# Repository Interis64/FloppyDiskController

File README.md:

# FloppyDiskController
 Floppy disk controller card for Interis 64

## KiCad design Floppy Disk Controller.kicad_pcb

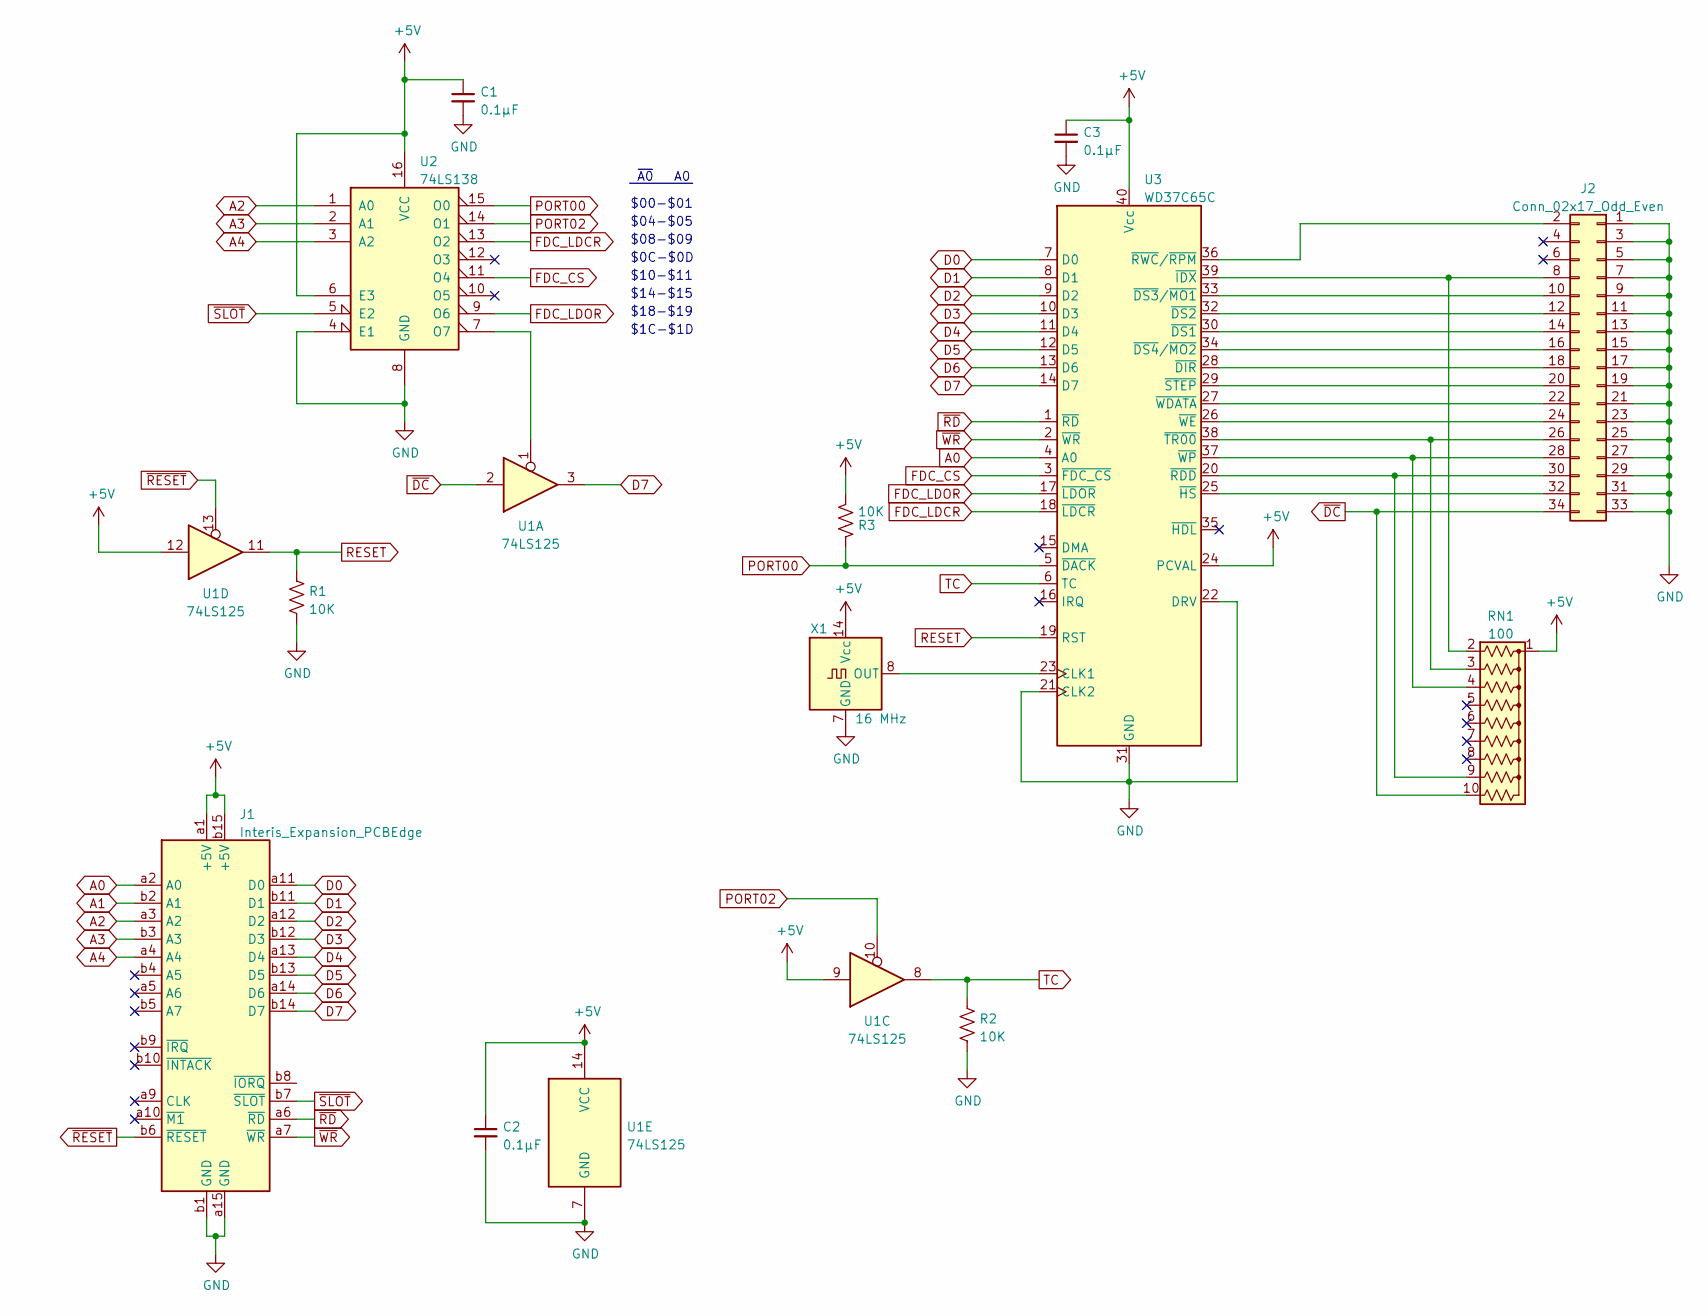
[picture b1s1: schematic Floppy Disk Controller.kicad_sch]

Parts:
C1, C2, C3: 0.1µF; C_Disc_D5.0mm_W2.5mm_P2.50mm
J1: Interis_Expansion_PCBEdge
J2: Conn_02x17_Odd_Even; IDC-Header_2x17_P2.54mm_Vertical
R1, R2, R3: 10K; R_Axial_DIN0207_L6.3mm_D2.5mm_P10.16mm_Horizontal
RN1: 100; R_Array_SIP10
U1: 74LS125; DIP-14_W7.62mm_Socket
U2: 74LS138; DIP-16_W7.62mm_Socket
U3: WD37C65C; DIP-40_W15.24mm_Socket
X1: 16 MHz; Oscillator_DIP-14

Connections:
+5V: C1.1, C2.1, C3.1, J1.a1 (+5V), J1.b15 (+5V), R3.1, RN1.1 (common), U1.9, U1.12, U1.14 (VCC), U2.6 (E3), U2.16 (VCC), U3.24 (PCVAL), U3.40 (Vcc), X1.14 (Vcc)
A0: J1.a2 (A0), U3.4 (A0)
A1: J1.b2 (A1)
A2: J1.a3 (A2), U2.1 (A0)
A3: J1.b3 (A3), U2.2 (A1)
A4: J1.a4 (A4), U2.3 (A2)
D0: J1.a11 (D0), U3.7 (D0)
D1: J1.b11 (D1), U3.8 (D1)
D2: J1.a12 (D2), U3.9 (D2)
D3: J1.b12 (D3), U3.10 (D3)
D4: J1.a13 (D4), U3.11 (D4)
D5: J1.b13 (D5), U3.12 (D5)
D6: J1.a14 (D6), U3.13 (D6)
D7: J1.b14 (D7), U1.3, U3.14 (D7)
FDC_CS: U2.11 (O4), U3.3 (~FDC_CS)
FDC_LDCR: U2.13 (O2), U3.18 (~LDCR)
FDC_LDOR: U2.9 (O6), U3.17 (~LDOR)
GND: C1.2, C2.2, C3.2, J1.a15 (GND), J1.b1 (GND), J2.1, J2.3, J2.5, J2.7, J2.9, J2.11, J2.13, J2.15, J2.17, J2.19, J2.21, J2.23, J2.25, J2.27, J2.29, J2.31, J2.33, R1.2, R2.1, U1.7 (GND), U2.4 (E1), U2.8 (GND), U3.21 (CLK2), U3.22 (DRV), U3.31 (GND), X1.7 (GND)
unnamed: J2.2, U3.36 (~RWC/~RPM)
unnamed: J2.8, RN1.2 (R1), U3.39 (~IDX)
unnamed: J2.10, U3.33 (~DS3/~MO1)
unnamed: J2.12, U3.32 (~DS2)
unnamed: J2.14, U3.30 (~DS1)
unnamed: J2.16, U3.34 (~DS4/~MO2)
unnamed: J2.18, U3.28 (~DIR)
unnamed: J2.20, U3.29 (~STEP)
unnamed: J2.22, U3.27 (~WDATA)
unnamed: J2.24, U3.26 (~WE)
unnamed: J2.26, RN1.3 (R2), U3.38 (~TR00)
unnamed: J2.28, RN1.4 (R3), U3.37 (~WP)
unnamed: J2.30, RN1.9 (R8), U3.20 (~RDD)
unnamed: J2.32, U3.25 (~HS)
unnamed: U1.1, U2.7 (O7)
unnamed: U3.23 (CLK1), X1.8 (OUT)
PORT00: R3.2, U2.15 (O0), U3.5 (~DACK)
PORT02: U1.10, U2.14 (O1)
RESET: R1.1, U1.11, U3.19 (RST)
TC: R2.2, U1.8, U3.6 (TC)
~DC: J2.34, RN1.10 (R9), U1.2
~RD: J1.a6 (~RD), U3.1 (~RD)
~RESET: J1.b6 (~RESET), U1.13
~SLOT: J1.b7 (~SLOT), U2.5 (E2)
~WR: J1.a7 (~WR), U3.2 (~WR)

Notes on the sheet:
$18-$19
$0C-$0D
$00-$01
~{A0} A0
$1C-$1D
$14-$15
$10-$11
$08-$09
$04-$05

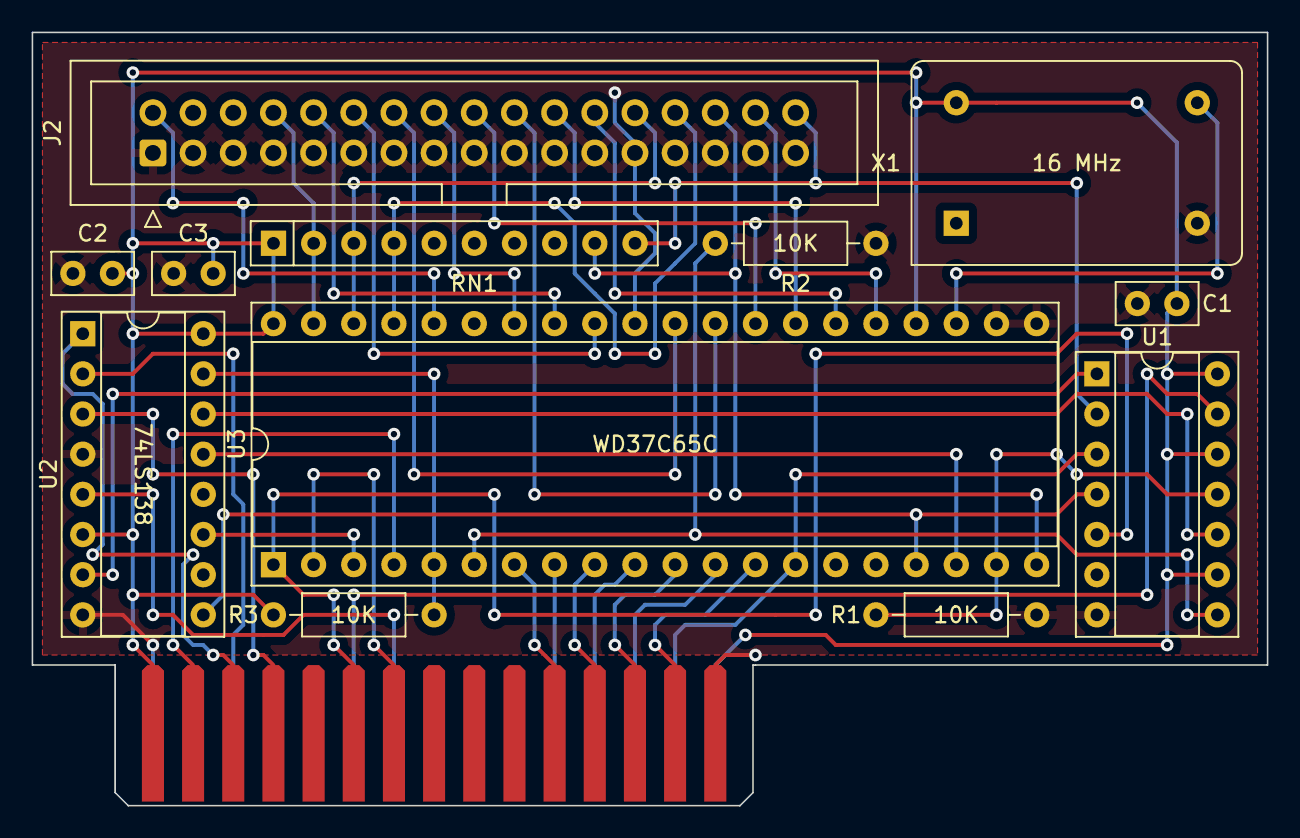
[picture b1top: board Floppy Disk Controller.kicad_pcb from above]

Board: 2 copper layers, 78.1 x 48.9 mm, 13 parts (0 on the bottom side), 42 nets.

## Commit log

2024-02-22 Updated schematic
